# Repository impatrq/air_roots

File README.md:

<div align="center">

# AIR ROOTS

</div>

## Descripcion

Es un sistema aeropónico  automatizado que cuenta con un sistema de recirculación de agua entre el tanque y el agua que no absorbieron las plantas, se puede utilizár en lugares donde no se pueda cultivar por suelos erosionados o agua contaminada.

## ¿Porque utilizarlo?

Porque el sistema presenta ventajas en el ahorro de costos y eficiencia, permite el ahorro de agua mediante el sistema de recirculacion que hace que el agua que las raices no absorban vuelva al tanque y al estar automatizado se pueden controlar los nutrientes que recibe la planta optimizando la salud y la calidad del cultivo

## ¿Donde utilizarlo?

Este sistema es ideal para areas donde el suelo impida el cultivo debido a la erosion o por la alta contaminacion del agua.
Tambien es empleable en lugares de poco espacio o uso hogareño 

## Pagina Web

Enlace: https://airoots22.github.io/

Enlace al repositorio: https://github.com/airoots22/airoots22.github.io

## Integrantes

* Mendez Alejandro 
    * alemendez1223@gmail.com
* Lopez Martinez Maximo
    * maximolopezmartino855@gmail.com
* Fachal Martino
    * martinofachal@gmail.com
* Ybañez Brenda
    * bredaybanez14@gmail.com
* Blanco Iara
    * iaraabrilblanco@gmail.com

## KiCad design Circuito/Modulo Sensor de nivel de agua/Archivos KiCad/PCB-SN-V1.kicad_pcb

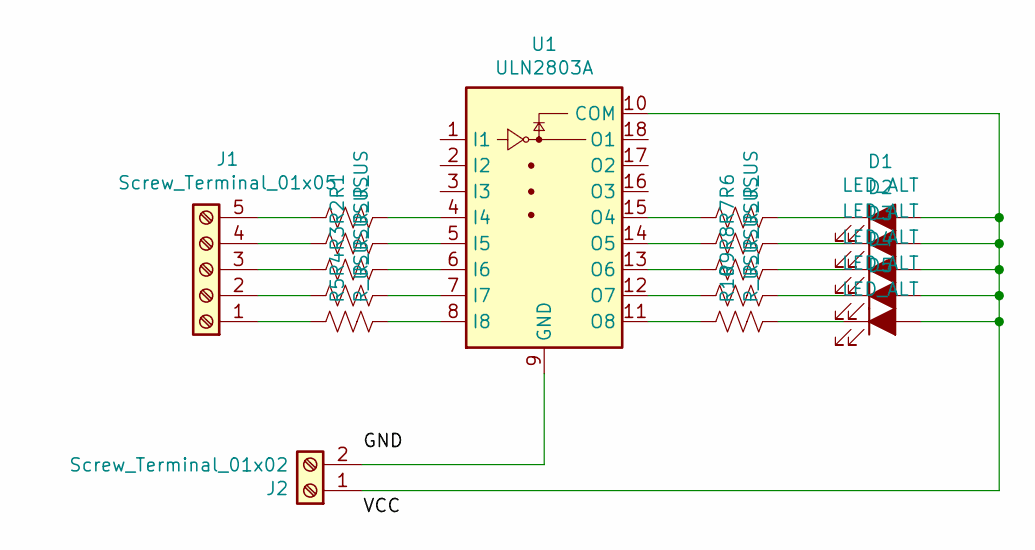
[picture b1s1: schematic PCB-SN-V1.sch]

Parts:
D1, D2, D3, D4, D5: LED_ALT; SolderWirePad_1x02_P3.81mm_Drill1mm
J1: Screw_Terminal_01x05; TerminalBlock_4Ucon_1x05_P3.50mm_Horizontal
J2: Screw_Terminal_01x02; TerminalBlock_4Ucon_1x02_P3.50mm_Horizontal
R1, R2, R3, R4, R5, R6, R7, R8, R9, R10: R_US; R_Axial_DIN0204_L3.6mm_D1.6mm_P7.62mm_Horizontal
U1: ULN2803A; DIP850W46P254L2324H393Q18

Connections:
unnamed: D1.1 (K), R6.2
unnamed: D1.2 (A), D2.2 (A), D3.2 (A), D4.2 (A), D5.2 (A), J2.1, U1.10 (COM)
unnamed: D2.1 (K), R7.2
unnamed: D3.1 (K), R8.2
unnamed: D4.1 (K), R9.2
unnamed: D5.1 (K), R10.2
unnamed: J1.1, R5.1
unnamed: J1.2, R4.1
unnamed: J1.3, R3.1
unnamed: J1.4, R2.1
unnamed: J1.5, R1.1
unnamed: J2.2, U1.9 (GND)
unnamed: R1.2, U1.4 (I4)
unnamed: R2.2, U1.5 (I5)
unnamed: R3.2, U1.6 (I6)
unnamed: R4.2, U1.7 (I7)
unnamed: R5.2, U1.8 (I8)
unnamed: R6.1, U1.15 (O4)
unnamed: R7.1, U1.14 (O5)
unnamed: R8.1, U1.13 (O6)
unnamed: R9.1, U1.12 (O7)
unnamed: R10.1, U1.11 (O8)

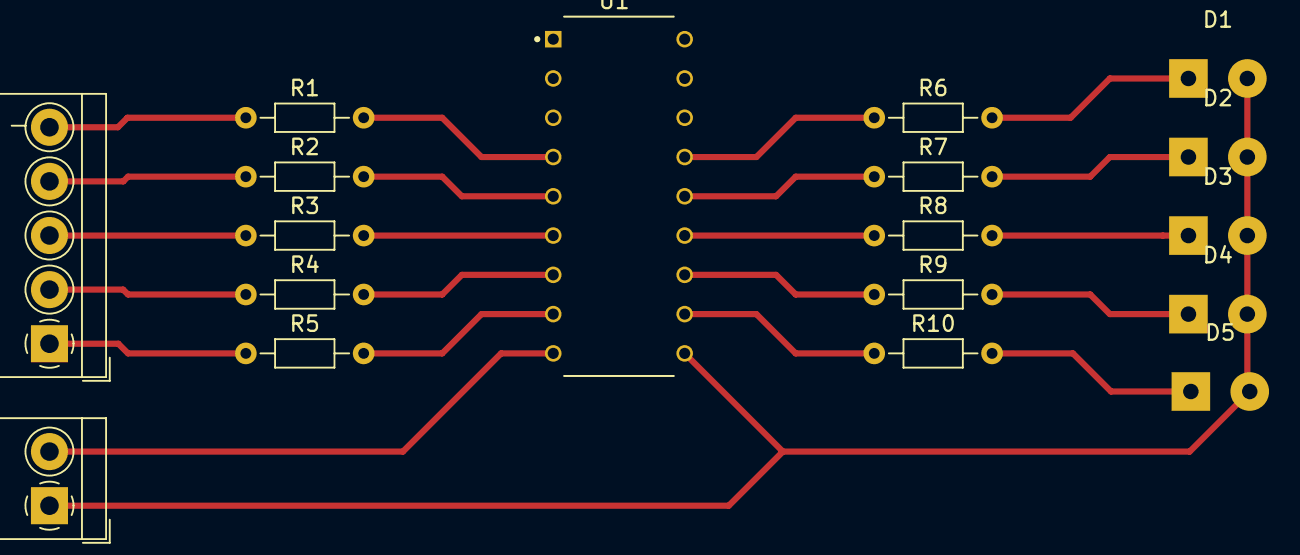
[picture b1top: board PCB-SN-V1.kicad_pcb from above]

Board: 2 copper layers, 18 parts (0 on the bottom side), 22 nets.

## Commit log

2022-06-03 docs: agregar datasheets del tcst1103 y LM741
2022-06-03 docs: agregar datasheets TCST1103, LM741
2022-06-03 docs: agregar Hardware raspberry pi pico
2022-06-03 docs: agregar carpeta Hardware y raspberry pi pico
2022-06-08 feat: agregar esquematico sensor turbidez y carpetas
2022-06-10 docs: agregar datasheet raspberry pi pico
2022-06-10 docs: agregar datasheet raspberry pi pico (#4)
2022-06-17 feat: agregar pcb y esq sensor de nivel de agua
2022-06-17 docs: agregar foto ULN2803
2022-08-12 feat: agregar esquematico y pcb nivel de agua
2022-08-12 docs: agregar foto lm741
2022-11-28 chore: eliminar archivos innecesarios
2022-11-28 chore: actualizar foto raspberry
2022-11-28 chore: eliminar foto obsoleta
2022-11-28 air_roots/Circuito/Modulo Sensor de turbidez/
2022-11-28 chore: eliminar foto obsoleta (#11)
2022-11-28 chore: actualizar foto raspberry (#10)
2022-11-28 chore: eliminar archivos innecesarios (#9)
2022-11-29 feat: agregar foto ntc
2022-11-29 feat: agregar readme
2022-12-03 chore: actualizar readme
